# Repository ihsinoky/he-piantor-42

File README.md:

# HE Piantor 42

42-key Hall-effect keyboard targeting a unified reverse-V assembly. D-015
defines reusable Main + Left/Right Wings; future Wing geometry must be
project-owned or explicitly approved.

> [!WARNING]
> **Experimental hardware:** Main Rev.4, Matrix Rev.3, Wing Rev.3 and the final
> case data are design baselines. No PCB has completed physical validation,
> and this repository does
> not describe a production-ready keyboard. Do not order or manufacture from
> the current files without completing the documented review gates.

## Target

- 42 keys
- Piantor-derived column-staggered layout
- Unified reverse-V keyboard assembly; modular Main + Wings
- Evaluate 17.0 / 16.5 / 16.0 mm pitch; production pitch remains open
- Full-height Hall-effect magnetic switches
- USB-C wired only
- Vial-compatible keymap, 4 layers
- Dedicated power indicator LED
- Separate layer indicator LED
- JLCPCB PCBA target
- FDM-printable enclosure

## Development flow

The design baseline is Main Rev.4 / Matrix Rev.3 / Wing Rev.3 / final case data.
Start with the [current artifacts index](docs/artifacts-index.md) for CAD,
manufacturing packages, case exports and recorded verification.
[Project status](docs/project-status.md) is authoritative for outstanding gates:
Order 1 awaits PO GO, production pitch awaits Matrix measurements, and physical
validation is pending. The [dashboard](task/index.html) shows the milestone plan
and current position as a non-authoritative read model.

## Contribution status

Public release is completed, as recorded in
[`docs/public-release-readiness.md`](docs/public-release-readiness.md).
JITX physical-backend evaluation concluded NO-GO (D-016); it is historical,
not an unresolved current design gate. Prospective contributors should start
with an Issue and follow
[`docs/development-workflow.md`](docs/development-workflow.md); a green CI run
does not replace Product Owner approval.

## Licensing

This is a mixed-license repository:

- project-authored hardware, mechanical, and manufacturing designs use
  CERN-OHL-P-2.0;
- project-authored firmware, software, scripts, dashboard, and documentation
  use the MIT License; and
- third-party files retain their original licenses and notices.

See the authoritative [`LICENSE.md`](LICENSE.md) path map, the full texts under
[`LICENSES/`](LICENSES/), and the canonical
[third-party inventory](hardware/lib/THIRD_PARTY.md). Items marked **REVIEW
REQUIRED** are public-release blockers, not an assertion of ownership.

Public-release audit evidence and the current Human Gate result are documented
in [`docs/public-release-readiness.md`](docs/public-release-readiness.md). This
repository has completed public release; the hardware remains experimental and
is not production-ready.

設計の世代・過去の試行・証跡は [履歴索引](docs/history-index.md) を参照。

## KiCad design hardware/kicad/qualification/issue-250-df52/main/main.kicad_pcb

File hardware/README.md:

# Hardware

現行は Main Rev.4／Matrix Rev.3／Wing Rev.3。CAD・回路源、単板とパネル、
ケース入力CSVは [成果物索引](../docs/artifacts-index.md) から正本へ進んでください。
Main は UDB C3 を別基板に持ち、左右Wingへ各200mmのハーネスで接続します。
Matrix は評価用18キー基板で、製品Wingとは別です。

設計採択と実機合格・発注GOは別です。[現行状態と残件](../docs/project-status.md)を参照。
`sensor-test/`、`main/`、旧Rev.M1やEDA評価の資料は設計履歴を含みます。

設計の世代・過去の試行・証跡は [履歴索引](../docs/history-index.md) を参照。

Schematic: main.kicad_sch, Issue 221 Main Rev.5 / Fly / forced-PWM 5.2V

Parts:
C1: 15pF; C1
C2: 15pF; C2
C3: 100nF; C3
C4: 100nF; C4
C5: 100nF; C5
C6: 100nF; C6
C7: 100nF; C7
C8: 100nF; C8
C9: 100nF; C9
C10: 100nF; C10
C11: 100nF; C11
C12: 1uF; C12
C13: 1uF; C13
C14: 10uF; C14
C15: 100nF; C15
C16: 1uF; C16
C17: 1uF; C17
C18: 1uF; C18
C19: 1uF; C19
C20: 1nF; C20
C21: 1nF; C21
C22: 1nF; C22
C23: 22uF 16V X6S 0805; C23
C24: 22uF 16V X6S 0805; C24
C25: 100nF; C25
C26: 22uF 16V X7R 1210; C26
C27: 22uF 16V X7R 1210; C27
C28: 22uF 16V X7R 1210; C28
H1: NPTH_2.2mm; H1
H2: NPTH_2.2mm; H2
H3: NPTH_2.2mm; H3
J2, J3: DF52-14S-0.8H(21); DF52-14S-0.8H_14
J4: 781710004; J4
L1: 1.5uH XFL4020-152MEC; L1
R3: 27; R3
R4: 27; R4
R5: 1k; R5
R6: 100k; R6
R7: 100k; R7
R8: 10k; R8
R9: 1k; R9
R10: 6.8k; R10
R11: 10k; R11
R12: 6.8k; R12
R13: 10k; R13
R14: 6.8k; R14
R15: 10k; R15
R16: 100k; R16
R17: 54.9k 0.1% 25ppm/K; R17
R18: 10k 0.1% 25ppm/K; R18
R19: 100k; R19
TP1: TestPoint; TP1
TP2: TestPoint; TP2
TP3: TestPoint; TP3
TP4: TestPoint; TP4
U1: RP2040; U1
U3: W25Q16JVUXIQ; U3
U4: AP2112K-3.3TRG1; U4
U5: TPS22919DCKR; U5
U6: TPS63070RNMR; U6
Y1: ABM8-272-T3; Y1

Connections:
ADC_A: C20.1, R10.2, R11.1, U1.38 (GPIO26/ADC0)
ADC_B: C21.1, R12.2, R13.1, U1.39 (GPIO27/ADC1)
ADC_C: C22.1, R14.2, R15.1, U1.40 (GPIO28/ADC2)
FB_5V2: R17.2, R18.1, U6.5 (FB)
GND: C1.2, C2.2, C3.2, C4.2, C5.2, C6.2, C7.2, C8.2, C9.2, C10.2, C11.2, C12.2, C13.2, C14.2, C15.2, C16.2, C17.2, C18.2, C19.2, C20.2, C21.2, C22.2, C23.2, C24.2, C25.2, C26.2, C27.2, C28.2, J2.2, J2.4, J2.8, J2.10, J2.12, J2.14, J3.2, J3.4, J3.8, J3.10, J3.12, J3.14, J4.4, R6.2, R7.2, R11.2, R13.2, R15.2, R16.2, R18.2, U1.19 (TESTEN), U1.57 (GND), U3.4 (GND), U4.2 (GND), U5.2 (GND), U6.1 (PS/SYNC), U6.4 (GND), U6.6 (FB2), U6.10 (PGND), U6.15 (VSEL), Y1.2 (G), Y1.4 (G)
HALL_5V: C19.1, J2.1, J3.1, U5.6 (OUT)
HALL_PWR_EN: R7.1, U1.9 (GPIO7), U5.3 (ON), U6.14 (EN)
MUX_A0: J2.3, J3.3, U1.4 (GPIO2)
MUX_A1: J2.5, J3.5, U1.5 (GPIO3)
MUX_A2: J2.6, J3.6, U1.6 (GPIO4)
MUX_EN1: J3.7, R16.1, U1.8 (GPIO6)
MUX_OUT_A: J2.9, J3.9, R10.1
MUX_OUT_B: J2.11, J3.11, R12.1
MUX_OUT_C: J2.13, J3.13, R14.1
QSPI_SCLK: U1.52 (QSPI_SCLK), U3.6 (CLK)
QSPI_SD0: U1.53 (QSPI_SD0), U3.5 (DI(IO0))
QSPI_SD1: U1.55 (QSPI_SD1), U3.2 (DO(IO1))
QSPI_SD2: U1.54 (QSPI_SD2), U3.3 (~WP(IO2))
QSPI_SD3: U1.51 (QSPI_SD3), U3.7 (~HOLD(IO3))
QSPI_SS_FLASH: R5.2, TP4.1, U3.1 (~CS)
QSPI_SS_MCU: R5.1, U1.56 (~QSPI_SS)
RAIL_PG: R19.2, U6.2 (PG)
RUN: R8.2, TP3.1, U1.26 (RUN)
SW1: L1.1, U6.11 (L1)
SW2: L1.2, U6.9 (L2)
SWCLK: TP2.1, U1.24 (SWCLK)
SWDIO: TP1.1, U1.25 (SWDIO)
USB_DM: R4.2, U1.46 (USB_DM)
USB_DM_ESD: J4.2, R4.1
USB_DP: R3.2, U1.47 (USB_DP)
USB_DP_ESD: J4.3, R3.1
V1V1: C11.1, C13.1, U1.23 (DVDD), U1.45 (VREG_VOUT), U1.50 (DVDD)
V3V3: C3.1, C4.1, C5.1, C6.1, C7.1, C8.1, C9.1, C10.1, C12.1, C14.1, C15.1, C17.1, R8.1, R19.1, U1.1 (IOVDD), U1.10 (IOVDD), U1.22 (IOVDD), U1.33 (IOVDD), U1.42 (IOVDD), U1.43 (ADC_AVDD), U1.44 (VREG_VIN), U1.48 (USB_VDD), U1.49 (IOVDD), U3.8 (VCC), U4.5 (VOUT)
V5V2: C26.1, C27.1, C28.1, R17.1, U5.1 (IN), U6.7 (VOUT), U6.8 (VOUT)
VAUX: C25.1, U6.3 (VAUX)
VBUS: C16.1, C18.1, C23.1, C24.1, J4.1, U4.1 (VIN), U4.3 (EN), U6.12 (VIN), U6.13 (VIN)
WING_EN: J2.7, R6.1, U1.7 (GPIO5)
XIN: C1.1, U1.20 (XIN), Y1.1
XOUT: R9.2, U1.21 (XOUT)
XOUT_XTAL: C2.1, R9.1, Y1.3

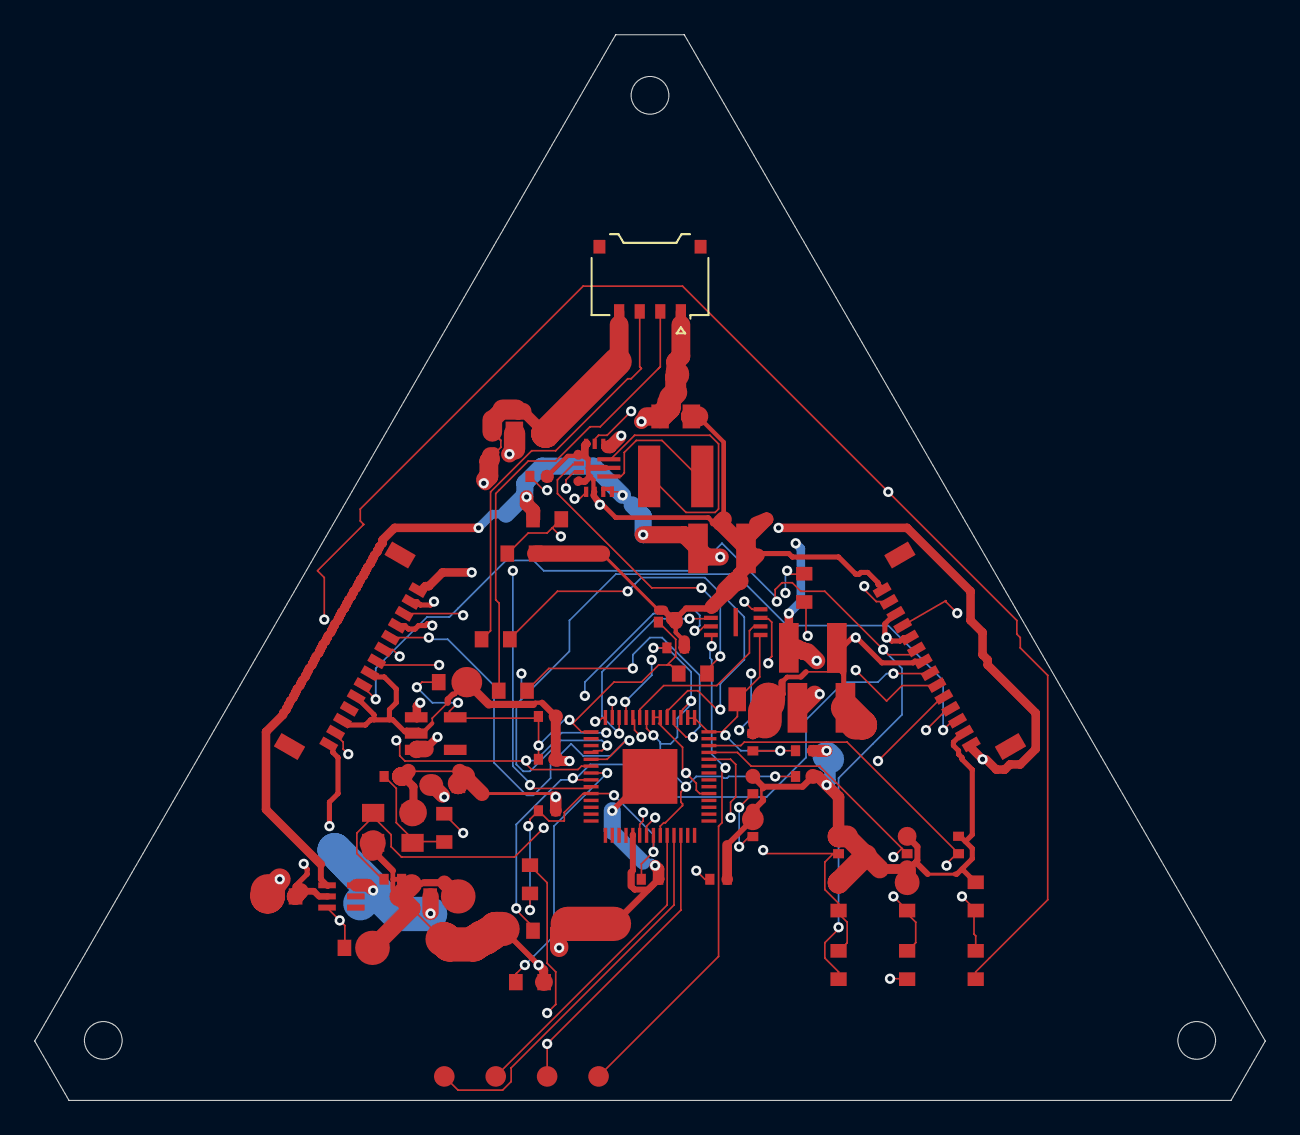
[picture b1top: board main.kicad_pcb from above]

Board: 4 copper layers, 71.8 x 62.2 mm, 62 parts (0 on the bottom side), 40 nets.

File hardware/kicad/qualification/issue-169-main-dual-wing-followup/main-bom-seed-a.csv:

ref,value,footprint,part_number,lcsc,assembled,source,procurement_confirmed
C1,15pF,Stage169:C1,0402CG150J500NT,C1548,True,Inherited #124 ledger,False
C10,100nF,Stage169:C10,CL05B104KO5NNNC,C1525,True,Inherited #124 ledger,False
C11,100nF,Stage169:C11,CL05B104KO5NNNC,C1525,True,Inherited #124 ledger,False
C12,1uF,Stage169:C12,CL05A105KA5NQNC,C52923,True,Inherited #124 ledger,False
C13,1uF,Stage169:C13,CL05A105KA5NQNC,C52923,True,Inherited #124 ledger,False
C14,10uF,Stage169:C14,CL21A106KAYNNNE,C15850,True,Inherited #124 ledger,False
C15,100nF,Stage169:C15,CL05B104KO5NNNC,C1525,True,Inherited #124 ledger,False
C16,1uF,Stage169:C16,CL10A105KB8NNNC,C15849,True,Inherited #124 ledger,False
C17,1uF,Stage169:C17,CL10A105KB8NNNC,C15849,True,Inherited #124 ledger,False
C18,1uF,Stage169:C18,CL10A105KB8NNNC,C15849,True,Inherited #124 ledger,False
C19,1uF,Stage169:C19,CL10A105KB8NNNC,C15849,True,Inherited #124 ledger,False
C2,15pF,Stage169:C2,0402CG150J500NT,C1548,True,Inherited #124 ledger,False
C20,1nF,Stage169:C20,0402B102K500NT,C1523,True,Inherited #124 ledger,False
C21,1nF,Stage169:C21,0402B102K500NT,C1523,True,Inherited #124 ledger,False
C22,1nF,Stage169:C22,0402B102K500NT,C1523,True,Inherited #124 ledger,False
C23,22uF 16V X6S 0805,Stage169:C23,GRM21BC81C226ME44L,C258782,True,Issue169 selected exact MPN; sourcing and manufacturer acceptance pending,False
C24,22uF 16V X6S 0805,Stage169:C24,GRM21BC81C226ME44L,C258782,True,Issue169 selected exact MPN; sourcing and manufacturer acceptance pending,False
C25,100nF,Stage169:C25,GRM155R71E104KE14D,C77014,True,Issue169 selected exact MPN; sourcing and manufacturer acceptance pending,False
C26,22uF 16V X6S 0805,Stage169:C26,GRM21BC81C226ME44L,C258782,True,Issue169 selected exact MPN; sourcing and manufacturer acceptance pending,False
C27,22uF 16V X6S 0805,Stage169:C27,GRM21BC81C226ME44L,C258782,True,Issue169 selected exact MPN; sourcing and manufacturer acceptance pending,False
C28,22uF 16V X6S 0805,Stage169:C28,GRM21BC81C226ME44L,C258782,True,Issue169 selected exact MPN; sourcing and manufacturer acceptance pending,False
C3,100nF,Stage169:C3,CL05B104KO5NNNC,C1525,True,Inherited #124 ledger,False
C4,100nF,Stage169:C4,CL05B104KO5NNNC,C1525,True,Inherited #124 ledger,False
C5,100nF,Stage169:C5,CL05B104KO5NNNC,C1525,True,Inherited #124 ledger,False
C6,100nF,Stage169:C6,CL05B104KO5NNNC,C1525,True,Inherited #124 ledger,False
C7,100nF,Stage169:C7,CL05B104KO5NNNC,C1525,True,Inherited #124 ledger,False
C8,100nF,Stage169:C8,CL05B104KO5NNNC,C1525,True,Inherited #124 ledger,False
C9,100nF,Stage169:C9,CL05B104KO5NNNC,C1525,True,Inherited #124 ledger,False
J1,TYPE-C-31-M-12,Stage169:J1,TYPE-C-31-M-12,C165948,True,Inherited #124 ledger,False
J2,BM14B-GHS-TBT(LF)(SN),Stage169:J2,BM14B-GHS-TBT(LF)(SN),C265384,True,Inherited #124 ledger,False
J3,BM14B-GHS-TBT(LF)(SN),Stage169:J3,BM14B-GHS-TBT(LF)(SN),C265384,True,Issue169 selected exact MPN; sourcing and manufacturer acceptance pending,False
L1,1.5uH XFL4020-152MEC,Stage169:L1,XFL4020-152MEC,C3033018,True,Issue169 selected exact MPN; sourcing and manufacturer acceptance pending,False
R1,5.1k,Stage169:R1,0603WAF5101T5E,C23186,True,Inherited #124 ledger,False
R10,6.8k,Stage169:R10,0603WAF6801T5E,C23212,True,Inherited #124 ledger,False
R11,10k,Stage169:R11,0603WAF1002T5E,C25804,True,Inherited #124 ledger,False
R12,6.8k,Stage169:R12,0603WAF6801T5E,C23212,True,Inherited #124 ledger,False
R13,10k,Stage169:R13,0603WAF1002T5E,C25804,True,Inherited #124 ledger,False
R14,6.8k,Stage169:R14,0603WAF6801T5E,C23212,True,Inherited #124 ledger,False
R15,10k,Stage169:R15,0603WAF1002T5E,C25804,True,Inherited #124 ledger,False
R16,100k,Stage169:R16,0603WAF1003T5E,C25803,True,Issue169 selected exact MPN; sourcing and manufacturer acceptance pending,False
R17,54.9k 0.1% 25ppm/K,Stage169:R17,TNPW060354K9BEEA,,True,Issue169 selected exact MPN; sourcing and manufacturer acceptance pending,False
R18,10k 0.1% 25ppm/K,Stage169:R18,TNPW060310K0BEEA,C844890,True,Issue169 selected exact MPN; sourcing and manufacturer acceptance pending,False
R19,100k,Stage169:R19,0603WAF1003T5E,C25803,True,Issue169 selected exact MPN; sourcing and manufacturer acceptance pending,False
R2,5.1k,Stage169:R2,0603WAF5101T5E,C23186,True,Inherited #124 ledger,False
R3,27,Stage169:R3,0603WAF270JT5E,C25190,True,Inherited #124 ledger,False
R4,27,Stage169:R4,0603WAF270JT5E,C25190,True,Inherited #124 ledger,False
R5,1k,Stage169:R5,0603WAF1001T5E,C21190,True,Inherited #124 ledger,False
R6,100k,Stage169:R6,0603WAF1003T5E,C25803,True,Inherited #124 ledger,False
R7,100k,Stage169:R7,0603WAF1003T5E,C25803,True,Inherited #124 ledger,False
R8,10k,Stage169:R8,0603WAF1002T5E,C25804,True,Inherited #124 ledger,False
R9,1k,Stage169:R9,0603WAF1001T5E,C21190,True,Inherited #124 ledger,False
TP1,TestPoint,Stage169:TP1,N/A (bare PCB test pad),N/A,False,Inherited #124 ledger,False
TP2,TestPoint,Stage169:TP2,N/A (bare PCB test pad),N/A,False,Inherited #124 ledger,False
TP3,TestPoint,Stage169:TP3,N/A (bare PCB test pad),N/A,False,Inherited #124 ledger,False
TP4,TestPoint,Stage169:TP4,N/A (bare PCB test pad),N/A,False,Inherited #124 ledger,False
U1,RP2040,Stage169:U1,RP2040,C2040,True,Inherited #124 ledger,False
U2,USBLC6-2SC6,Stage169:U2,USBLC6-2SC6,C7519,True,Inherited #124 ledger,False
U3,W25Q16JVUXIQ,Stage169:U3,W25Q16JVUXIQ,C2843335,True,Inherited #124 ledger,False
U4,AP2112K-3.3TRG1,Stage169:U4,AP2112K-3.3TRG1,C51118,True,Inherited #124 ledger,False
U5,TPS22919DCKR,Stage169:U5,TPS22919DCKR,C2149796,True,Inherited #124 ledger,False
U6,TPS63070RNMR,Stage169:U6,TPS63070RNMR,C109322,True,Issue169 selected exact MPN; sourcing and manufacturer acceptance pending,False
Y1,ABM8-272-T3,Stage169:Y1,ABM8-272-T3,C20625731,True,Inherited #124 ledger,False

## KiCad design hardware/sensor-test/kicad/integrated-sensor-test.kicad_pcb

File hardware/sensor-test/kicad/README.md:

# Sensor-test KiCad project

This directory contains the electrical design for the four-key Hall evaluation board.

## Integrated design

`integrated-sensor-test.kicad_sch` is the review and PCB-source schematic. It combines:

- the RP2040 core, flash, crystal, BOOTSEL, RUN/reset and SWD access from the
  Raspberry Pi minimal-design baseline;
- the USB-C sink, USB ESD, 3.3 V regulator and always-on power indicator;
- switched `HALL_5V`, four DRV5055 sensors, TMUX1208, and the protected
  `ADC_SENSE` input; and
- a GPIO11 evaluation-status LED. The production layer RGB LED (`GPIO8`–`GPIO10`)
  remains reserved and is deliberately not fitted on this evaluation board.

The Hall control nets are connected directly at the RP2040 pins rather than via
an external-controller placeholder: GPIO2=`MUX_A0`, GPIO3=`MUX_A1`,
GPIO4=`MUX_A2`, GPIO5=`MUX_EN0`, GPIO7=`HALL_PWR_EN`, and GPIO26/ADC0=`ADC_SENSE`.

The three older schematics remain as traceable source blocks and standalone ERC
fixtures. Do not use them independently as the PCB source.

## Footprint dependency bootstrap

`footprint-dependencies.json` is mechanically generated from the integrated
schematic by `inventory_footprints.py`. The manually dispatched
`bootstrap-kicad-footprints` workflow exports only the listed official
footprints from `kicad/kicad:9.0.9`. It discovers and validates each source path
inside the image rather than assuming the image layout, preserves the exported
bytes, and publishes provenance plus SHA-256 hashes in the
`issue-11-kicad-9.0.9-footprints` artifact. The workflow runs automatically on
the Issue #11 pull request (and can also be dispatched manually) and includes
the license/attribution file supplied by the image package.

The artifact must be reviewed and copied to
`hardware/lib/third_party/kicad-9-footprints/` before the standard logical
libraries can be rebound in `fp-lib-table`. Do not substitute generated or
look-alike geometry when the official artifact is unavailable.

## Scope

This milestone stops at an ERC-clean integrated schematic. PCB placement,
routing, Gerbers and assembly outputs are intentionally deferred. Do not order
boards from this directory yet.

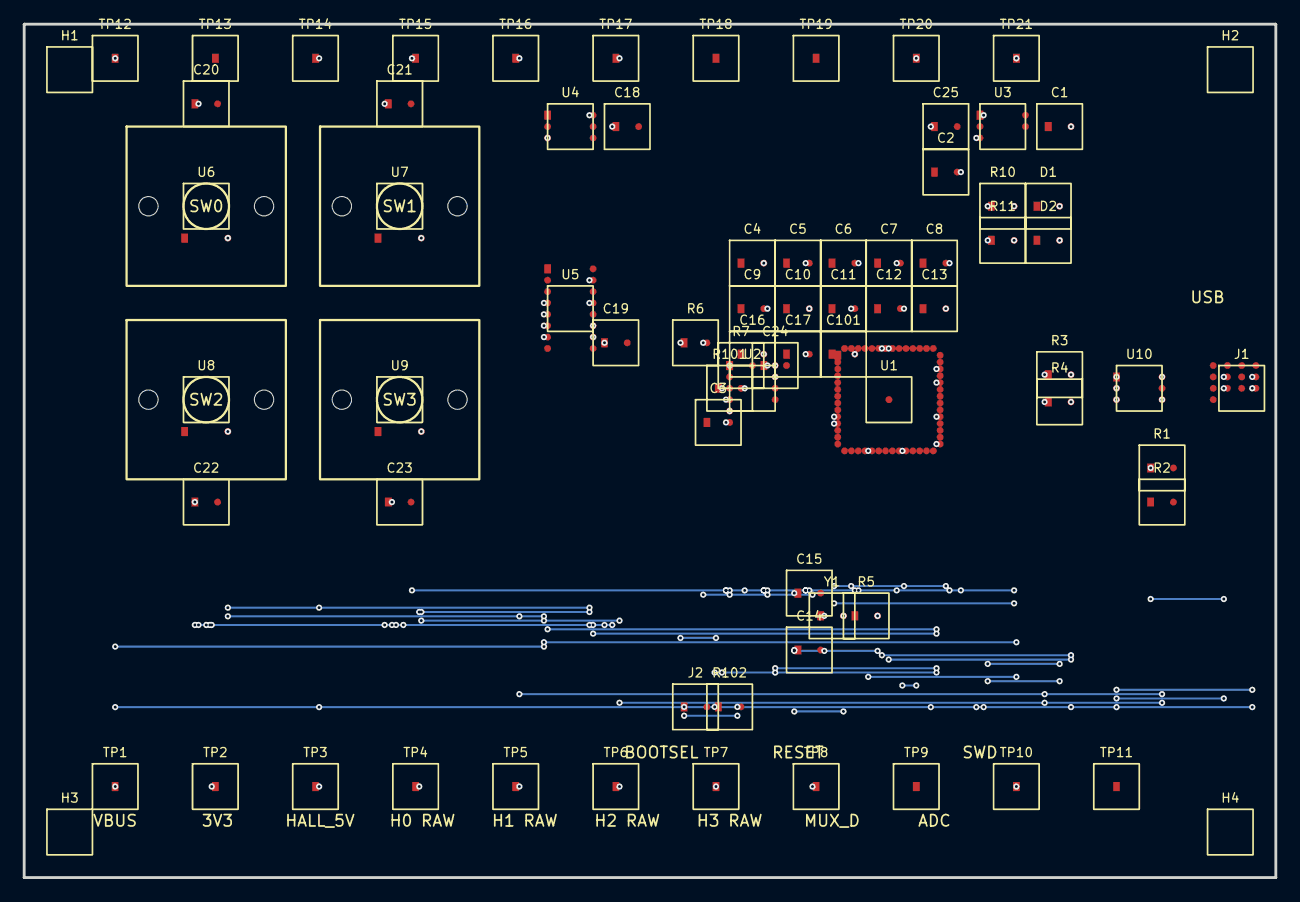
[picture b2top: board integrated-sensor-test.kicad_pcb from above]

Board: 4 copper layers, 110.0 x 75.0 mm, 77 parts (0 on the bottom side), 32 nets.

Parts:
C1, C2, C18, C25: 1u; C_0603_1608Metric
C3, C4, C5, C6, C7, C8, C10, C12, C13, C16: 100n; C_0402_1005Metric
C9, C11: 1u; C_0402_1005Metric
C14, C15: 15p; C_0402_1005Metric
C17, C101: 10u; C_0805_2012Metric
C19, C20, C21, C22, C23: 100n; C_0603_1608Metric
C24: 1n; C_0603_1608Metric
D1: POWER_GREEN; LED_0603_1608Metric
D2: STATUS_GREEN; LED_0603_1608Metric
H1, H2, H3, H4: MountingHole; MountingHole_2.7mm_M2.5
J1: TYPE-C-31-M-12; USB_C_Receptacle_HRO_TYPE-C-31-M-12
J2: Conn_01x02; PinHeader_1x02_P2.54mm_Vertical
R1, R2: 5.1k; R_0603_1608Metric
R3, R4: 27; C_0402_1005Metric
R5: 1k; R_0402_1005Metric
R6: 6.8k; R_0603_1608Metric
R7: 10k; R_0603_1608Metric
R10, R11: 1.5k; R_0603_1608Metric
R101: DNF; C_0402_1005Metric
R102: 1k; C_0402_1005Metric
TP1, TP14: VBUS; TestPoint_Pad_D1.5mm
TP2: HALL_5V; TestPoint_Pad_D1.5mm
TP3: H0_RAW; TestPoint_Pad_D1.5mm
TP4: H1_RAW; TestPoint_Pad_D1.5mm
TP5: H2_RAW; TestPoint_Pad_D1.5mm
TP6: H3_RAW; TestPoint_Pad_D1.5mm
TP7: MUX_D; TestPoint_Pad_D1.5mm
TP8: ADC_SENSE; TestPoint_Pad_D1.5mm
TP9, TP18: GND; TestPoint_Pad_D1.5mm
TP10: MUX_S5_SPARE; TestPoint_Pad_D1.5mm
TP11: MUX_S6_SPARE; TestPoint_Pad_D1.5mm
TP12: MUX_S7_SPARE; TestPoint_Pad_D1.5mm
TP13: MUX_S8_SPARE; TestPoint_Pad_D1.5mm
TP15: +3V3; TestPoint_Pad_D1.5mm
TP16: USB_D+_PROTECTED; TestPoint_Pad_D1.5mm
TP17: USB_D-_PROTECTED; TestPoint_Pad_D1.5mm
TP19: SWDIO; TestPoint_Pad_D1.5mm
TP20: SWCLK; TestPoint_Pad_D1.5mm
TP21: RUN; TestPoint_Pad_D1.5mm
U1: RP2040; RP2040-QFN-56
U2: W25Q16JVUXIQ; USON-8_UX_2x3x0p6_WIN
U3: AP2112K-3.3TRG1; SOT-23-5
U4: TPS22919DCKR; SOT-363_SC-70-6
U5: TMUX1208PWR; TSSOP-16_4.4x5mm_P0.65mm
U6, U7, U8, U9: DRV5055A3QDBZR; SW_MX_HE_0deg_1u
U10: USBLC6-2SC6; SOT-23-6
Y1: ABM8-272-T3; Crystal_SMD_Abracon_ABM8G-2Pin_3.2x2.5mm

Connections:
+1V1: C11.2, C12.2, C13.2, U1.19
+3V3: C2.2, C3.2, C4.2, C5.2, C6.2, C7.2, C8.2, C9.2, C10.2, C16.2, C17.2, C101.2, R10.2, R101.2, TP15.1, U2.4, U2.9
ADC_SENSE: C24.1, R6.2, R7.1, TP8.1
CC1: J1.A7, R1.1
GND: C1.1, C2.1, C3.1, C4.1, C5.1, C6.1, C7.1, C8.1, C9.1, C10.1, C11.1, C12.1, C13.1, C14.2, C15.2, C16.1, C17.1, C18.2, C19.2, C20.2, C21.2, C22.2, C23.2, C24.2, C25.2, C101.1, D1.1, D2.1, R1.2, R2.2, R7.2, TP9.1, TP18.1, U1.45, U2.8, U5.13, U6.1, U7.1, U8.1, U9.1, U10.5
GPIO11: R11.2, U1.18
H0_RAW: TP3.1, U5.10, U6.2
H1_RAW: TP4.1, U5.12, U7.2
H2_RAW: TP5.1, U5.7, U8.2
H3_RAW: TP6.1, U5.6, U9.2
HALL_5V: C18.1, C19.1, C20.1, C21.1, C22.1, C23.1, TP2.1, U4.4, U5.14, U6.3, U7.3, U8.3, U9.3
HALL_PWR_EN: U1.30, U4.3
MUX_A2: U1.34, U5.15
MUX_D: R6.1, TP7.1
MUX_S5_SPARE: TP10.1, U5.5
MUX_S7_SPARE: TP12.1, U5.4
unnamed: C14.1, R5.2, Y1.1
unnamed: R4.2, U1.40
unnamed: R3.2, U1.41
PWR_LED_A: D1.2, R10.1
QSPI_SD3: U1.26, U2.5
QSPI_SS: R101.1, R102.1, U1.24, U2.6
RUN: TP21.1, U1.51
STATUS_LED_A: D2.2, R11.1
SWCLK: TP20.1, U1.56
USB_D+_CONN: J1.A6, U10.1
USB_D+_PROTECTED: R3.1, TP16.1, U10.6
USB_D-_CONN: J1.A5, U10.3
USB_D-_PROTECTED: R4.1, TP17.1, U10.4
VBUS: C1.2, C25.1, J1.A8, TP1.1, TP14.1, U3.1, U3.3, U10.2
XIN: C15.1, Y1.2
~USB_BOOT: J2.1, R102.2

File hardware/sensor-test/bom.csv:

block,reference,qty,manufacturer,mpn,lcsc,package,value_or_note,population
MCU,U1,1,Raspberry Pi,RP2040,C2040,LQFN-56,MCU,baseline
Flash,U2,1,Winbond,W25Q16JVUXIQ,C2843335,USON-8-EP(2x3),16Mbit QSPI,baseline
Crystal,Y1,1,Abracon,ABM8-272-T3,C20625731,SMD3225-4P,12MHz 10pF,baseline
Logic regulator,U3,1,Diodes Inc.,AP2112K-3.3TRG1,C51118,SOT-25-5,3.3V 600mA,baseline
Logic regulator input capacitor,C1,1,TBD,TBD,TBD,0603,1uF X7R VBUS-to-GND,baseline
Logic regulator output capacitor,C2,1,TBD,TBD,TBD,0603,1uF X7R 3V3-to-GND,baseline
Hall load switch,U4,1,Texas Instruments,TPS22919DCKR,C2149796,SC-70-6,switched HALL_5V,baseline
Hall switch input decoupling,C25,1,TBD,TBD,TBD,0603,1uF X7R VBUS-to-GND,baseline
Hall rail bulk/decoupling,C18,1,TBD,TBD,TBD,0603,1uF X7R HALL_5V-to-GND,baseline
Analog mux,U5,1,Texas Instruments,TMUX1208PWR,C494728,TSSOP-16,8:1 mux,baseline
Hall sensor,U6-U9,4,Texas Instruments,DRV5055A3QDBZR,C266128,SOT-23,+/-85mT 25mV/mT@5V,reference build
USB connector,J1,1,Korean Hroparts Elec,TYPE-C-31-M-12,C165948,SMD,USB-C 16P,baseline
USB ESD,U10,1,STMicroelectronics,USBLC6-2SC6,C7519,SOT-23-6L,USB 2.0 two-line ESD protection,baseline
USB CC resistors,R1 R2,2,TBD,TBD,TBD,0603,5.1k 1%,baseline
USB series resistors,R3 R4,2,TBD,TBD,TBD,0603,27R 1%,baseline
Crystal series resistor,R5,1,TBD,TBD,TBD,0603,1k 1%,baseline
Flash decoupling,C3,1,TBD,TBD,TBD,0402,100nF X7R,baseline
RP2040 high-frequency decoupling,C4-C8 C10 C12 C13 C16,9,TBD,TBD,TBD,0402,100nF X7R,baseline
RP2040 regulator decoupling,C9 C11,2,TBD,TBD,TBD,0402,1uF X7R,baseline
RP2040 bulk capacitor,C17,1,TBD,TBD,TBD,0805,10uF X7R,baseline
QSPI optional resistor,R8,1,TBD,TBD,TBD,0603,DNF,do not fit
BOOTSEL series resistor,R9,1,TBD,TBD,TBD,0603,1k 1%,baseline
Crystal load capacitors,C14 C15,2,TBD,TBD,TBD,0402,15pF C0G,baseline
ADC divider top,R6,1,TBD,TBD,TBD,0603,6.8k 1%,baseline
ADC divider bottom,R7,1,TBD,TBD,TBD,0603,10k 1%,baseline
ADC filter,C24,1,TBD,TBD,TBD,0603,1nF C0G/X7R,baseline
Hall decoupling,C20-C23,4,TBD,TBD,TBD,0603,100nF X7R,baseline
Mux decoupling,C19,1,TBD,TBD,TBD,0603,100nF X7R,baseline
Power LED,D1,1,TBD,TBD,TBD,0603,green,baseline
Power LED resistor,R10,1,TBD,TBD,TBD,0603,1.5k target <1mA,baseline
Status LED,D2,1,TBD,TBD,TBD,0603,GPIO11 diagnostic LED,baseline
Status LED resistor,R11,1,TBD,TBD,TBD,0603,1.5k target <1mA,baseline
BOOTSEL switch,SW1,1,TBD,TBD,TBD,PTS810-compatible SMD tact,QSPI_SS to GND through R9,baseline
RESET switch,SW2,1,TBD,TBD,TBD,PTS810-compatible SMD tact,RUN to GND,baseline

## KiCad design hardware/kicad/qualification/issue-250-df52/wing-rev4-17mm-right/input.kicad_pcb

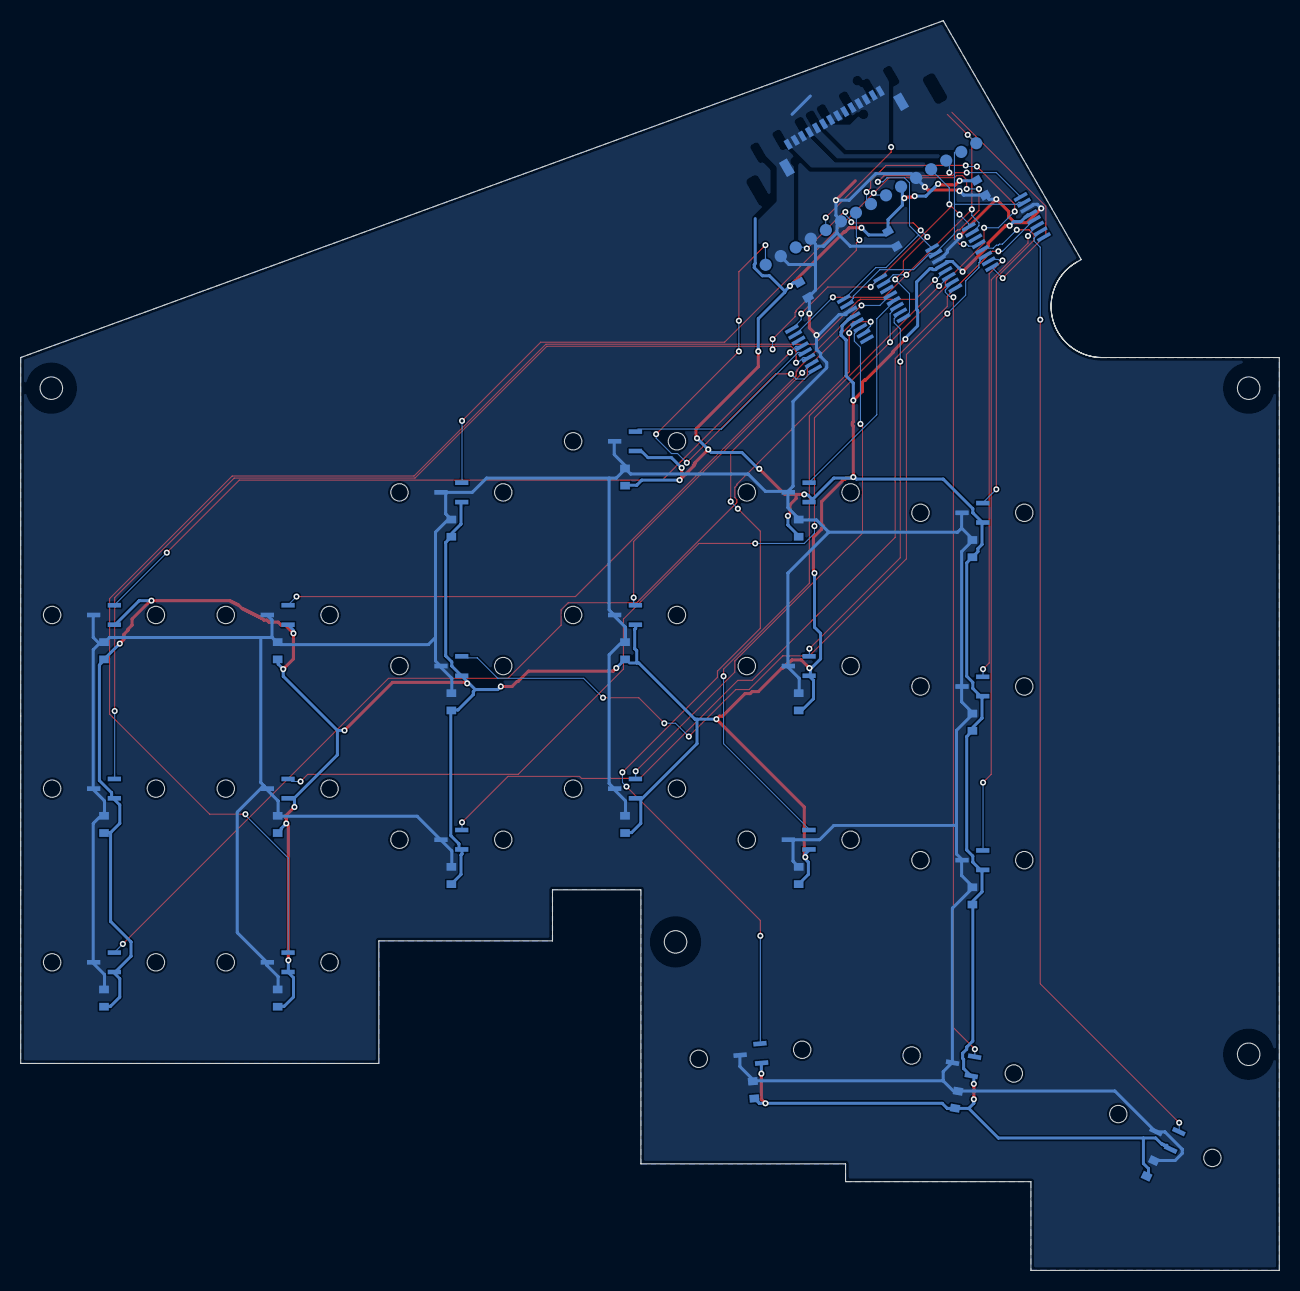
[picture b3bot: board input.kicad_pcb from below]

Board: 2 copper layers, 123.2 x 122.3 mm, 110 parts (64 on the bottom side), 30 nets.

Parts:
C_HA0, C_HA1, C_HA2, C_HA3, C_HA4, C_HA5, C_HA6: GRM188R71C104KA01D; capacitor
C_HB0, C_HB1, C_HB2, C_HB3, C_HB4, C_HB5, C_HB6: GRM188R71C104KA01D; capacitor
C_HC0, C_HC1, C_HC2, C_HC3, C_HC4, C_HC5, C_HC6: GRM188R71C104KA01D; capacitor
C_MUX_A: GRM188R71C104KA01D; capacitor
C_MUX_B: GRM188R71C104KA01D; capacitor
C_MUX_C: GRM188R71C104KA01D; capacitor
H1, H2, H3, H4: NPTH_2.2; NPTH
J_WING: DF52-14S-0.8H(21); DF52-14S-0.8H_14
MH_1_1, MH_1_2, MH_2_1, MH_2_2, MH_3_1, MH_3_2, MH_4_1, MH_4_2, MH_5_1, MH_5_2, MH_6_1, MH_6_2, MH_7_1, MH_7_2, MH_8_1, MH_8_2, MH_9_1, MH_9_2, MH_10_1, MH_10_2, MH_11_1, MH_11_2, MH_12_1, MH_12_2, MH_13_1, MH_13_2, MH_14_1, MH_14_2, MH_15_1, MH_15_2, MH_16_1, MH_16_2, MH_17_1, MH_17_2, MH_18_1, MH_18_2, MH_19_1, MH_19_2, MH_20_1, MH_20_2, MH_21_1, MH_21_2: NPTH_1.7; NPTH
TP_H_CTR_RAW: PCB_PAD_1.2MM; testpoint
TP_H_DIAG_RAW: PCB_PAD_1.2MM; testpoint
TP_H_N_RAW: PCB_PAD_1.2MM; testpoint
TP_W_A0, TP_W_A1, TP_W_A2: PCB_PAD_1.2MM; testpoint
TP_W_EN: PCB_PAD_1.2MM; testpoint
TP_W_GND: PCB_PAD_1.2MM; testpoint
TP_W_GND_A: PCB_PAD_1.2MM; testpoint
TP_W_GND_B: PCB_PAD_1.2MM; testpoint
TP_W_GND_C: PCB_PAD_1.2MM; testpoint
TP_W_H5V: PCB_PAD_1.2MM; testpoint
TP_W_MUXA: PCB_PAD_1.2MM; testpoint
TP_W_MUXB: PCB_PAD_1.2MM; testpoint
TP_W_MUXC: PCB_PAD_1.2MM; testpoint
U_HA0, U_HA1, U_HA2, U_HA3, U_HA4, U_HA5, U_HA6: DRV5055A3QDBZR; hall
U_HB0, U_HB1, U_HB2, U_HB3, U_HB4, U_HB5, U_HB6: DRV5055A3QDBZR; hall
U_HC0, U_HC1, U_HC2, U_HC3, U_HC4, U_HC5, U_HC6: DRV5055A3QDBZR; hall
U_MUX_A: TMUX1208PWR; mux
U_MUX_B: TMUX1208PWR; mux
U_MUX_C: TMUX1208PWR; mux

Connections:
GND: C_HA0.2, C_HA1.2, C_HA2.2, C_HA3.2, C_HA4.2, C_HA5.2, C_HA6.2, C_HB0.2, C_HB1.2, C_HB2.2, C_HB3.2, C_HB4.2, C_HB5.2, C_HB6.2, C_HC0.2, C_HC1.2, C_HC2.2, C_HC3.2, C_HC4.2, C_HC5.2, C_HC6.2, C_MUX_A.2, C_MUX_B.2, C_MUX_C.2, J_WING.2, J_WING.4, J_WING.8, J_WING.10, J_WING.12, J_WING.14, TP_W_GND.1, TP_W_GND_A.1, TP_W_GND_B.1, TP_W_GND_C.1, U_HA0.3, U_HA1.3, U_HA2.3, U_HA3.3, U_HA4.3, U_HA5.3, U_HA6.3, U_HB0.3, U_HB1.3, U_HB2.3, U_HB3.3, U_HB4.3, U_HB5.3, U_HB6.3, U_HC0.3, U_HC1.3, U_HC2.3, U_HC3.3, U_HC4.3, U_HC5.3, U_HC6.3, U_MUX_A.14, U_MUX_B.14, U_MUX_C.14
HALL_5V: C_HA0.1, C_HA1.1, C_HA2.1, C_HA3.1, C_HA4.1, C_HA5.1, C_HA6.1, C_HB0.1, C_HB1.1, C_HB2.1, C_HB3.1, C_HB4.1, C_HB5.1, C_HB6.1, C_HC0.1, C_HC1.1, C_HC2.1, C_HC3.1, C_HC4.1, C_HC5.1, C_HC6.1, C_MUX_A.1, C_MUX_B.1, C_MUX_C.1, J_WING.1, TP_W_H5V.1, U_HA0.1, U_HA1.1, U_HA2.1, U_HA3.1, U_HA4.1, U_HA5.1, U_HA6.1, U_HB0.1, U_HB1.1, U_HB2.1, U_HB3.1, U_HB4.1, U_HB5.1, U_HB6.1, U_HC0.1, U_HC1.1, U_HC2.1, U_HC3.1, U_HC4.1, U_HC5.1, U_HC6.1, U_MUX_A.13, U_MUX_B.13, U_MUX_C.13
H_A0_RAW: U_HA0.2, U_MUX_A.4
H_A1_RAW: U_HA1.2, U_MUX_A.5
H_A2_RAW: TP_H_CTR_RAW.1, U_HA2.2, U_MUX_A.6
H_A3_RAW: U_HA3.2, U_MUX_A.7
H_A4_RAW: U_HA4.2, U_MUX_A.12
H_A5_RAW: U_HA5.2, U_MUX_A.11
H_A6_RAW: U_HA6.2, U_MUX_A.10
H_B0_RAW: U_HB0.2, U_MUX_B.4
H_B1_RAW: U_HB1.2, U_MUX_B.5
H_B2_RAW: TP_H_N_RAW.1, U_HB2.2, U_MUX_B.6
H_B3_RAW: U_HB3.2, U_MUX_B.7
H_B4_RAW: U_HB4.2, U_MUX_B.12
H_B5_RAW: U_HB5.2, U_MUX_B.11
H_B6_RAW: U_HB6.2, U_MUX_B.10
H_C0_RAW: TP_H_DIAG_RAW.1, U_HC0.2, U_MUX_C.4
H_C1_RAW: U_HC1.2, U_MUX_C.5
H_C2_RAW: U_HC2.2, U_MUX_C.6
H_C3_RAW: U_HC3.2, U_MUX_C.7
H_C4_RAW: U_HC4.2, U_MUX_C.12
H_C5_RAW: U_HC5.2, U_MUX_C.11
H_C6_RAW: U_HC6.2, U_MUX_C.10
MUX_A0: J_WING.3, TP_W_A0.1, U_MUX_A.1, U_MUX_B.1, U_MUX_C.1
MUX_A1: J_WING.5, TP_W_A1.1, U_MUX_A.16, U_MUX_B.16, U_MUX_C.16
MUX_A2: J_WING.6, TP_W_A2.1, U_MUX_A.15, U_MUX_B.15, U_MUX_C.15
MUX_OUT_A: J_WING.9, TP_W_MUXA.1, U_MUX_A.8
MUX_OUT_B: J_WING.11, TP_W_MUXB.1, U_MUX_B.8
MUX_OUT_C: J_WING.13, TP_W_MUXC.1, U_MUX_C.8
WING_EN: J_WING.7, TP_W_EN.1, U_MUX_A.2, U_MUX_B.2, U_MUX_C.2

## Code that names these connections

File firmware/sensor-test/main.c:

#include <stdbool.h>
#include <stdint.h>
#include <stdio.h>

#include "hardware/adc.h"
#include "pico/stdio_usb.h"
#include "pico/stdlib.h"

enum {
    PIN_MUX_A0 = 2,
    PIN_MUX_A1 = 3,
    PIN_MUX_A2 = 4,
    PIN_MUX_EN0 = 5,
    PIN_HALL_PWR_EN = 7,
    PIN_STATUS_LED = 11,
    PIN_ADC0 = 26,
};

enum {
    ADC_INPUT_0 = 0,
    MUX_ADDRESS_COUNT = 4,
    MUX_SETTLE_US = 20,
    ADC_SAMPLES_PER_KEY = 8,
    USB_WAIT_MS = 3000,
    HALL_POWER_SETTLE_MS = 10,
    FRAME_PERIOD_MS = 10,
};

static void init_output(uint pin, bool value) {
    gpio_init(pin);
    gpio_set_dir(pin, GPIO_OUT);
    gpio_put(pin, value);
}

static void mux_set_address(uint8_t address) {
    gpio_put(PIN_MUX_A0, (address >> 0) & 1u);
    gpio_put(PIN_MUX_A1, (address >> 1) & 1u);
    gpio_put(PIN_MUX_A2, (address >> 2) & 1u);
}

static uint16_t read_adc_average(void) {
    // First conversion after an analog-mux transition is intentionally discarded.
    (void)adc_read();

    uint32_t sum = 0;
    for (uint i = 0; i < ADC_SAMPLES_PER_KEY; ++i) {
        sum += adc_read();
    }
    return (uint16_t)((sum + ADC_SAMPLES_PER_KEY / 2u) / ADC_SAMPLES_PER_KEY);
}

int main(void) {
    // Keep the Hall rail and mux disabled from the first software-controlled state.
    init_output(PIN_HALL_PWR_EN, false);
    init_output(PIN_MUX_EN0, false);
    init_output(PIN_MUX_A0, false);
    init_output(PIN_MUX_A1, false);
    init_output(PIN_MUX_A2, false);
    init_output(PIN_STATUS_LED, false);

    adc_init();
    adc_gpio_init(PIN_ADC0);
    adc_select_input(ADC_INPUT_0);

    stdio_init_all();

    // Give USB CDC time to enumerate, but do not require a host for board operation.
    absolute_time_t usb_deadline = make_timeout_time_ms(USB_WAIT_MS);
    while (!stdio_usb_connected() && !time_reached(usb_deadline)) {
        sleep_ms(10);
    }

    gpio_put(PIN_HALL_PWR_EN, true);
    sleep_ms(HALL_POWER_SETTLE_MS);
    gpio_put(PIN_MUX_EN0, true);
    gpio_put(PIN_STATUS_LED, true);

    printf("# he-piantor-42 sensor-test\n");
    printf("# settle_us=%u,samples_per_key=%u\n", MUX_SETTLE_US, ADC_SAMPLES_PER_KEY);
    printf("timestamp_us,key,mux_address,adc_raw,hall_power,test_marker\n");

    while (true) {
        absolute_time_t frame_start = get_absolute_time();

        for (uint8_t address = 0; address < MUX_ADDRESS_COUNT; ++address) {
            mux_set_address(address);
            busy_wait_us_32(MUX_SETTLE_US);

            const uint16_t raw = read_adc_average();
            const uint64_t timestamp_us = time_us_64();

            printf("%llu,%u,%u,%u,1,stream\n",
                   (unsigned long long)timestamp_us,
                   (unsigned)address,
                   (unsigned)address,
                   (unsigned)raw);
        }

        // Keep the initial logger bandwidth modest and deterministic.
        const int64_t elapsed_us = absolute_time_diff_us(frame_start, get_absolute_time());
        const int64_t target_us = (int64_t)FRAME_PERIOD_MS * 1000;
        if (elapsed_us < target_us) {
            sleep_us((uint32_t)(target_us - elapsed_us));
        }
    }
}
